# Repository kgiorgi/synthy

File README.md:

# synthy

Synthy is a small 8-step synth with no microcontroller and no code. It plays a looping melody of 8 notes, and you set each note by turning its own knob. Everything runs off USB-C.

How it works

One 555 timer ticks like a metronome. Every tick moves a 4017 counter on to the next step, so the 8 steps light up one after another and then start over.

Each step has its own knob, LED and switch. When a step is active, its knob sets how fast a second 555 timer buzzes, and that's the note you hear. The LED shows which step is playing, and the switch can turn a step off so it becomes a rest.

The sound then goes through a tone knob that goes from soft to buzzy, a volume knob, and a small LM386 amplifier that drives a speaker.

How to play it

Plug in USB-C and the loop starts.

Turn the 8 step knobs to change the notes. TEMPO changes the speed. TONE makes the sound softer or buzzier, and VOLUME sets how loud it is.

Flip the small switches by the LEDs to turn steps into rests and make rhythms. The 4/8 switch picks a 4-step or 8-step loop, and RUN/STOP freezes the loop on one note so you can tune it.

Before drawing the board

I built both timers in a circuit simulator first to check the numbers. The tone timer covers about 210 Hz to 1.5 kHz, which is roughly three octaves, and the clock goes from about 1.3 to 13 steps per second. Both matched what I calculated, so I didn't need to change any part values. The simulation file is in the sim folder.

Parts

The main parts are two LMC555 timers, a 74HC4017 counter, an LM386 amplifier, 11 knobs, 9 LEDs, 8 diodes, an 8-way DIP switch, two slide switches, a USB-C socket and a small 8 ohm speaker. The full list with LCSC part numbers is in production/BOM.csv.

I bought the knobs myself on AliExpress because LCSC was out of stock. If the LMC555 sells out, two regular NE555s plus a 74HCT4017 work in the same spots.

Testing it after building

The chips go in sockets, so the board can be tested one part at a time.

With no chips in, plug in USB-C. The power LED should light, and every chip socket should have about 5 V.
Put in the clock and the counter. The step LEDs should walk from 1 to 8 and repeat, TEMPO should change the speed, and RUN/STOP should freeze it.
Put in the tone timer and the amplifier. The speaker should play the loop, each knob should change its own note, and a step with its switch off should be silent.

If something fails, only that one part of the circuit needs checking.

Files

hardware/kicad has the KiCad project. production has the gerbers and the BOM. docs/images has the render and schematic. sim has the simulator file.

What I learned

First of all measuring frequencies in circuits. A little bit niche but at least it wasn't difficult to understand unlike well, copper layers in kicad? I still can't even begin to explain what was happening towards the end but I got the intuition which is sufficient for me.

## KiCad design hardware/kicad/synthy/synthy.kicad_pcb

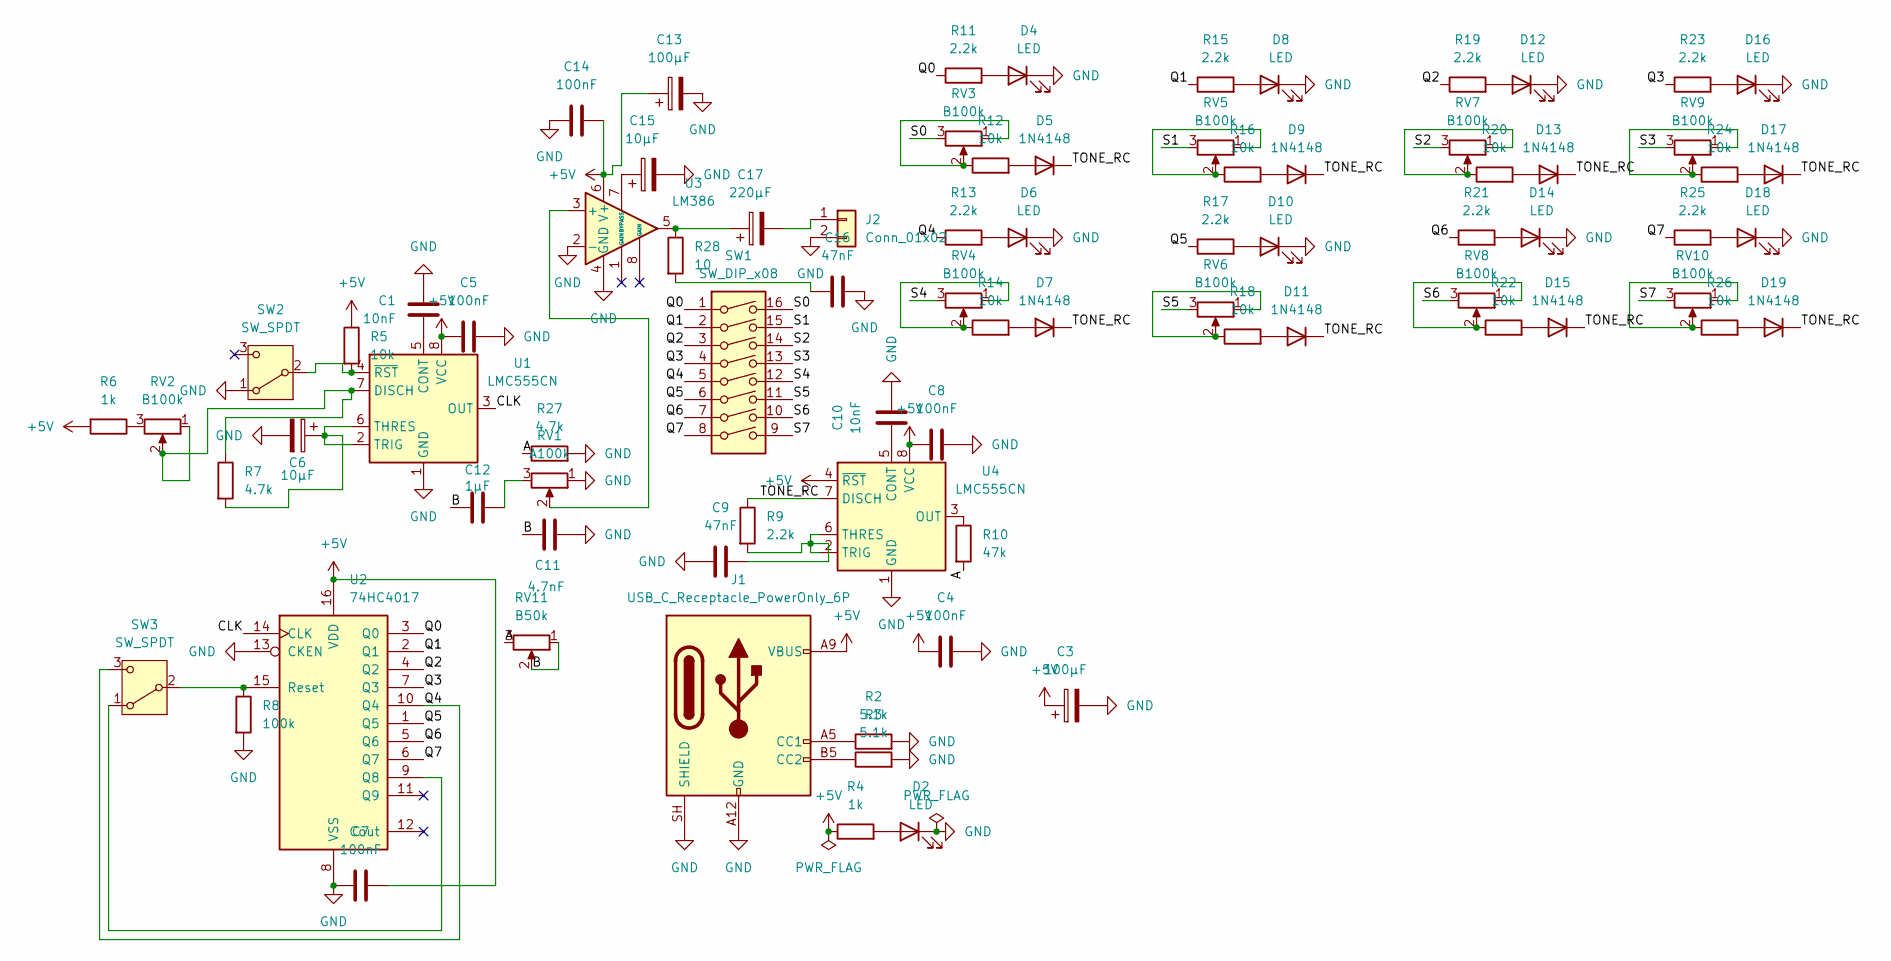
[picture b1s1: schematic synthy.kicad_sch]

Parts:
C1, C10: 10nF; C_Disc_D5.0mm_W2.5mm_P5.00mm
C3, C13: 100µF; CP_Radial_D6.3mm_P2.50mm
C4, C5, C7, C8, C14: 100nF; C_Disc_D5.0mm_W2.5mm_P5.00mm
C6, C15: 10µF; CP_Radial_D5.0mm_P2.00mm
C9: 47nF; C_Rect_L7.2mm_W2.5mm_P5.00mm_FKS2_FKP2_MKS2_MKP2
C11: 4.7nF; C_Disc_D5.0mm_W2.5mm_P5.00mm
C12: 1µF; C_Disc_D5.0mm_W2.5mm_P5.00mm
C16: 47nF; C_Disc_D5.0mm_W2.5mm_P5.00mm
C17: 220µF; CP_Radial_D8.0mm_P3.50mm
D2, D4, D6, D8, D10, D12, D14, D16, D18: LED; LED_D3.0mm
D5, D7, D9, D11, D13, D15, D17, D19: 1N4148; D_DO-35_SOD27_P2.54mm_Vertical_AnodeUp
J1: USB_C_Receptacle_PowerOnly_6P; USB_C_Receptacle_GCT_USB4125-xx-x-0190_6P_TopMnt_Horizontal
J2: Conn_01x02; JST_PH_B2B-PH-K_1x02_P2.00mm_Vertical
R2, R3: 5.1k; R_Axial_DIN0207_L6.3mm_D2.5mm_P10.16mm_Horizontal
R4, R6: 1k; R_Axial_DIN0207_L6.3mm_D2.5mm_P10.16mm_Horizontal
R5: 10k; R_Axial_DIN0207_L6.3mm_D2.5mm_P10.16mm_Horizontal
R7, R27: 4.7k; R_Axial_DIN0207_L6.3mm_D2.5mm_P10.16mm_Horizontal
R8: 100k; R_Axial_DIN0207_L6.3mm_D2.5mm_P10.16mm_Horizontal
R9: 2.2k; R_Axial_DIN0207_L6.3mm_D2.5mm_P10.16mm_Horizontal
R10: 47k; R_Axial_DIN0207_L6.3mm_D2.5mm_P10.16mm_Horizontal
R11, R13, R15, R17, R19, R21, R23, R25: 2.2k; R_Axial_DIN0207_L6.3mm_D2.5mm_P2.54mm_Vertical
R12, R14, R16, R18, R20, R22, R24, R26: 10k; R_Axial_DIN0207_L6.3mm_D2.5mm_P2.54mm_Vertical
R28: 10; R_Axial_DIN0207_L6.3mm_D2.5mm_P10.16mm_Horizontal
RV1: A100k; Potentiometer_Alps_RK09K_Single_Vertical
RV2, RV3, RV4, RV5, RV6, RV7, RV8, RV9, RV10: B100k; Potentiometer_Alps_RK09K_Single_Vertical
RV11: B50k; Potentiometer_Alps_RK09K_Single_Vertical
SW1: SW_DIP_x08; SW_DIP_SPSTx08_Slide_9.78x22.5mm_W7.62mm_P2.54mm
SW2, SW3: SW_SPDT; SW_Slide_SPDT_Straight_CK_OS102011MS2Q
U1, U4: LMC555CN; DIP-8_W7.62mm_Socket
U2: 74HC4017; DIP-16_W7.62mm_Socket
U3: LM386; DIP-8_W7.62mm_Socket

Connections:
+5V: C3.1, C4.1, C5.1, C7.2, C8.2, C13.1, C14.1, J1.A9 (VBUS), J1.B9 (VBUS), R4.1, R5.1, R6.2, U1.8 (VCC), U2.16 (VDD), U3.6 (V+), U4.4 (~RST), U4.8 (VCC)
/A: R10.2, R27.1, RV11.3
/B: C11.2, C12.1, RV11.1, RV11.2
/CLK: U1.3 (OUT), U2.14 (CLK)
/Q0: R11.1, SW1.1, U2.3 (Q0)
/Q1: R15.1, SW1.2, U2.2 (Q1)
/Q2: R19.1, SW1.3, U2.4 (Q2)
/Q3: R23.1, SW1.4, U2.7 (Q3)
/Q4: R13.1, SW1.5, SW3.3 (C), U2.10 (Q4)
/Q5: R17.1, SW1.6, U2.1 (Q5)
/Q6: R21.1, SW1.7, U2.5 (Q6)
/Q7: R25.1, SW1.8, U2.6 (Q7)
/S0: RV3.3, SW1.16
/S1: RV5.3, SW1.15
/S2: RV7.3, SW1.14
/S3: RV9.3, SW1.13
/S4: RV4.3, SW1.12
/S5: RV6.3, SW1.11
/S6: RV8.3, SW1.10
/S7: RV10.3, SW1.9
/TONE_RC: D5.1 (K), D7.1 (K), D9.1 (K), D11.1 (K), D13.1 (K), D15.1 (K), D17.1 (K), D19.1 (K), R9.1, U4.7 (DISCH)
GND: C1.2, C3.2, C4.2, C5.2, C6.2, C7.1, C8.1, C9.2, C10.2, C11.1, C13.2, C14.2, C15.2, C16.2, D2.1 (K), D4.1 (K), D6.1 (K), D8.1 (K), D10.1 (K), D12.1 (K), D14.1 (K), D16.1 (K), D18.1 (K), J1.A12 (GND), J1.B12 (GND), J1.SH (SHIELD), J2.2, R2.2, R3.2, R8.2, R27.2, RV1.1, SW2.1 (A), U1.1 (GND), U2.8 (VSS), U2.13 (CKEN), U3.2 (-), U3.4 (GND), U4.1 (GND)
unnamed: C12.2, RV1.3
unnamed: C16.1, R28.2
unnamed: C17.1, R28.1, U3.5
unnamed: D2.2 (A), R4.2
unnamed: D4.2 (A), R11.2
unnamed: D5.2 (A), R12.2
unnamed: D6.2 (A), R13.2
unnamed: D7.2 (A), R14.2
unnamed: D8.2 (A), R15.2
unnamed: D9.2 (A), R16.2
unnamed: D10.2 (A), R17.2
unnamed: D11.2 (A), R18.2
unnamed: D12.2 (A), R19.2
unnamed: D13.2 (A), R20.2
unnamed: D14.2 (A), R21.2
unnamed: D15.2 (A), R22.2
unnamed: D16.2 (A), R23.2
unnamed: D17.2 (A), R24.2
unnamed: D18.2 (A), R25.2
unnamed: D19.2 (A), R26.2
unnamed: J1.A5 (CC1), R2.1
unnamed: J1.B5 (CC2), R3.1
unnamed: C17.2, J2.1
unnamed: R6.1, RV2.3
unnamed: R12.1, RV3.1, RV3.2
unnamed: R14.1, RV4.1, RV4.2
unnamed: R16.1, RV5.1, RV5.2
unnamed: R18.1, RV6.1, RV6.2
unnamed: R20.1, RV7.1, RV7.2
unnamed: R22.1, RV8.1, RV8.2
unnamed: R24.1, RV9.1, RV9.2
unnamed: R26.1, RV10.1, RV10.2
unnamed: R5.2, SW2.2 (B), U1.4 (~RST)
unnamed: SW3.1 (A), U2.9 (Q8)
unnamed: R8.1, SW3.2 (B), U2.15 (Reset)
unnamed: C1.1, U1.5 (CONT)
unnamed: R7.1, RV2.1, RV2.2, U1.7 (DISCH)
unnamed: C6.1, R7.2, U1.2 (TRIG), U1.6 (THRES)
unnamed: RV1.2, U3.3 (+)
unnamed: C15.1, U3.7 (BYPASS)
unnamed: C10.1, U4.5 (CONT)
unnamed: R10.1, U4.3 (OUT)
unnamed: C9.1, R9.2, U4.2 (TRIG), U4.6 (THRES)

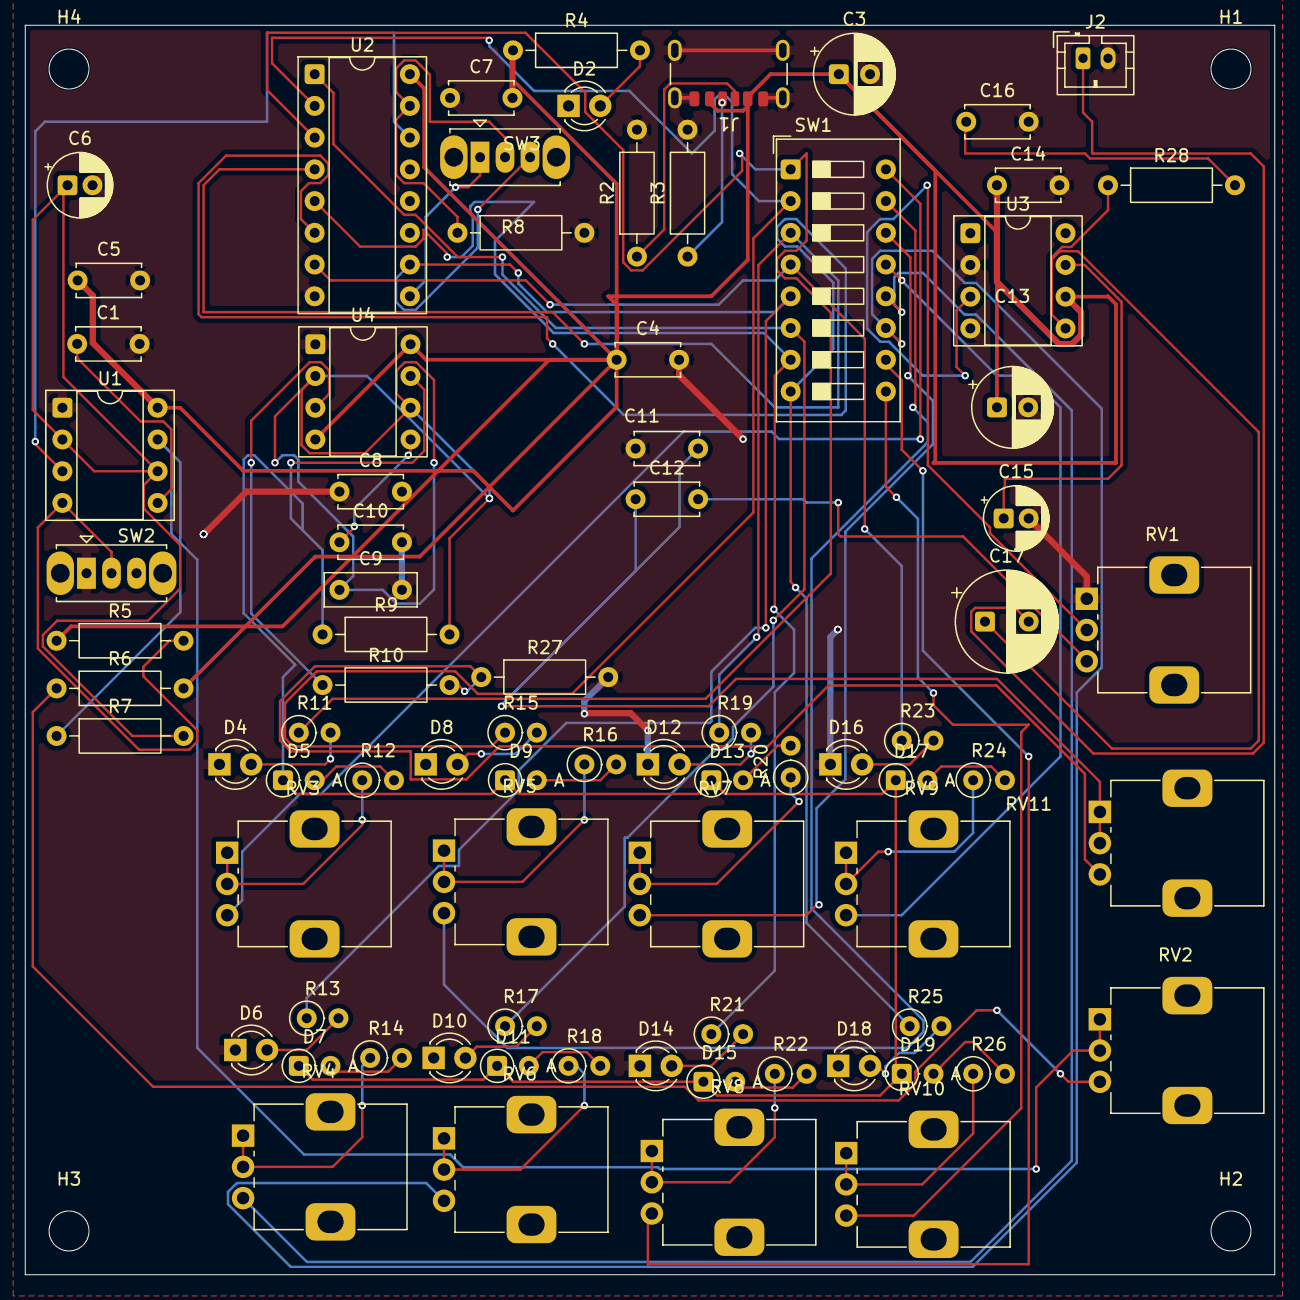
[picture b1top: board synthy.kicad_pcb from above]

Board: 2 copper layers, 100.0 x 100.0 mm, 84 parts (0 on the bottom side), 65 nets.

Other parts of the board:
H1, H2, H3, H4: MountingHole_3.2mm_M3
